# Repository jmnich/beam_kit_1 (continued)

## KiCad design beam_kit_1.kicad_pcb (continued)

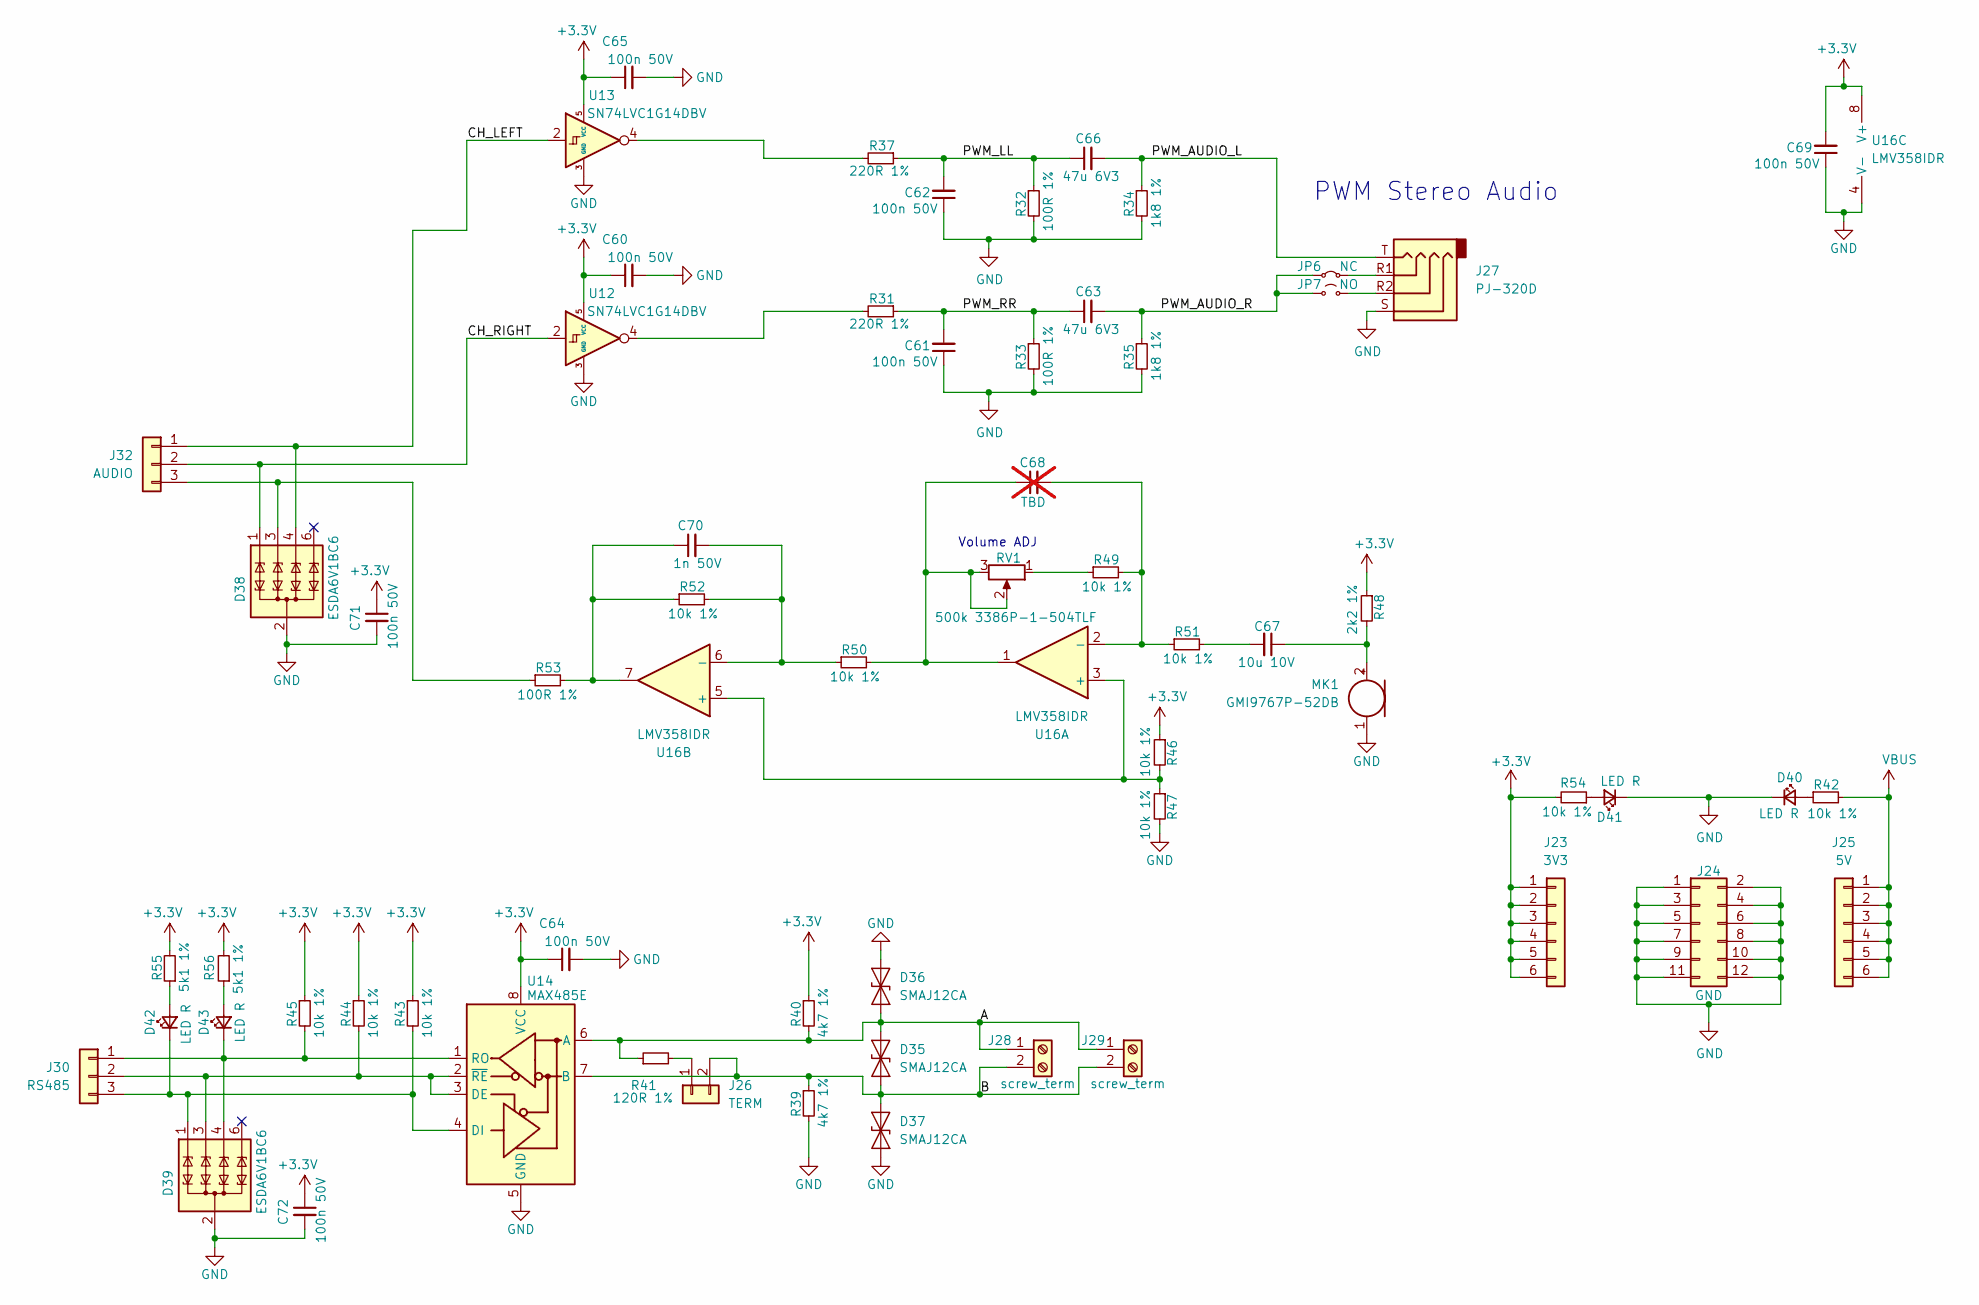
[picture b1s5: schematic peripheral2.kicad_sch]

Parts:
C60, C61, C62, C64, C65, C69, C71, C72: 100n 50V; C_0603_1608Metric_Pad1.08x0.95mm_HandSolder; jlc C14663
C63, C66: 47u 6V3; C_0805_2012Metric; jlc C16780
C67: 10u 10V; C_0603_1608Metric_Pad1.08x0.95mm_HandSolder; jlc C19702
C68: TBD; C_0603_1608Metric_Pad1.08x0.95mm_HandSolder; not fitted
C70: 1n 50V; C_0603_1608Metric_Pad1.08x0.95mm_HandSolder; jlc C1588
D35, D36, D37: SMAJ12CA; D_SMA; jlc C908818
D38, D39: ESDA6V1BC6; SOT-23-6; MPN ESDA6V1BC6; jlc C495220
D40, D41, D42, D43: LED R; LED_0603_1608Metric_Pad1.05x0.95mm_HandSolder; jlc C2286
J23: 3V3; PinHeader_1x06_P2.54mm_Vertical; jlc C37208
J24: GND; PinHeader_2x06_P2.54mm_Vertical; jlc C492423
J25: 5V; PinHeader_1x06_P2.54mm_Vertical; jlc C37208
J26: TERM; PinHeader_1x02_P2.54mm_Vertical; jlc C492401
J27: PJ-320D; Jack_3.5mm_PJ320D_Horizontal; jlc C431535
J28, J29: screw_term; TerminalBlock_Phoenix_MKDS-1,5-2-5.08_1x02_P5.08mm_Horizont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; jlc C395734
J30: RS485; PinHeader_1x03_P2.54mm_Vertical; jlc C49257
J32: AUDIO; PinHeader_1x03_P2.54mm_Vertical; jlc C49257
JP6: NC; SolderJumper-2_P1.3mm_Bridged_RoundedPad1.0x1.5mm
JP7: NO; SolderJumper-2_P1.3mm_Open_RoundedPad1.0x1.5mm
MK1: GMI9767P-52DB; PinHeader_1x02_P2.54mm_Vertical; jlc C234023
R31, R37: 220R 1%; R_0603_1608Metric_Pad0.98x0.95mm_HandSolder; jlc C22962
R32, R33, R53: 100R 1%; R_0603_1608Metric_Pad0.98x0.95mm_HandSolder; jlc C22775
R34, R35: 1k8 1%; R_0603_1608Metric_Pad0.98x0.95mm_HandSolder; jlc C4177
R39, R40: 4k7 1%; R_0603_1608Metric_Pad0.98x0.95mm_HandSolder; jlc C23162
R41: 120R 1%; R_0603_1608Metric_Pad0.98x0.95mm_HandSolder; jlc C22787
R42, R43, R44, R45, R46, R47, R49, R50, R51, R52, R54: 10k 1%; R_0603_1608Metric_Pad0.98x0.95mm_HandSolder; jlc C25804
R48: 2k2 1%; R_0603_1608Metric_Pad0.98x0.95mm_HandSolder; jlc C4190
R55, R56: 5k1 1%; R_0603_1608Metric_Pad0.98x0.95mm_HandSolder; jlc C23186
RV1: 500k 3386P-1-504TLF; Potentiometer_Bourns_3386P_Vertical; jlc C116316
U12, U13: SN74LVC1G14DBV; SOT-23-5; MPN SN74LVC1G14DBV; jlc C7835
U14: MAX485E; SOIC-8_3.9x4.9mm_P1.27mm; jlc C19738
U16: LMV358IDR; SOIC-8_3.9x4.9mm_P1.27mm; jlc C63813

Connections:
+3.3V: C60.1, C64.1, C65.1, C69.2, C71.1, C72.1, J23.1, J23.2, J23.3, J23.4, J23.5, J23.6, R40.1, R43.1, R44.1, R45.1, R46.1, R48.1, R54.2, R55.2, R56.2, U12.5 (VCC), U13.5 (VCC), U14.8 (VCC), U16.8 (V+); also elsewhere on the board
/peripheral2/A: D35.2 (A2), D36.1 (A1), J28.1, J29.1, R40.2, R41.1, U14.6 (A)
/peripheral2/B: D35.1 (A1), D37.2 (A2), J26.2, J28.2, J29.2, R39.1, U14.7 (B)
/peripheral2/CH_LEFT: D38.4 (TVS3), J32.1, U13.2
/peripheral2/CH_RIGHT: D38.1 (TVS1), J32.2, U12.2
/peripheral2/PWM_AUDIO_L: C66.2, J27.T, R34.1
/peripheral2/PWM_AUDIO_R: C63.2, JP6.1 (A), JP7.1 (A), R35.1
/peripheral2/PWM_LL: C62.2, C66.1, R32.1, R37.1
/peripheral2/PWM_RR: C61.2, C63.1, R31.1, R33.1
GND: C60.2, C61.1, C62.1, C64.2, C65.2, C69.1, C71.2, C72.2, D36.2 (A2), D37.1 (A1), D38.2 (COM), D38.5 (COM), D39.2 (COM), D39.5 (COM), D40.1 (K), D41.1 (K), J24.1, J24.2, J24.3, J24.4, J24.5, J24.6, J24.7, J24.8, J24.9, J24.10, J24.11, J24.12, J27.S, MK1.1 (-), R32.2, R33.2, R34.2, R35.2, R39.2, R47.2, U12.3 (GND), U13.3 (GND), U14.5 (GND), U16.4 (V-); also elsewhere on the board
unnamed: C67.2, R51.2
unnamed: C68.1, R50.2, RV1.2, RV1.3, U16.1
unnamed: C70.1, R52.1, R53.2, U16.7
unnamed: D38.3 (TVS2), J32.3, R53.1
unnamed: D39.1 (TVS1), D42.1 (K), J30.3, R43.2, U14.4 (DI)
unnamed: D39.3 (TVS2), J30.2, R44.2, U14.2 (~RE), U14.3 (DE)
unnamed: D39.4 (TVS3), D43.1 (K), J30.1, R45.2, U14.1 (RO)
unnamed: D40.2 (A), R42.1
unnamed: D41.2 (A), R54.1
unnamed: D42.2 (A), R55.1
unnamed: D43.2 (A), R56.1
unnamed: J26.1, R41.2
unnamed: J27.R1, JP6.2 (B)
unnamed: J27.R2, JP7.2 (B)
unnamed: C67.1, MK1.2 (+), R48.2
unnamed: R31.2, U12.4
unnamed: R37.2, U13.4
unnamed: R49.1, RV1.1
unnamed: R46.2, R47.1, U16.3 (+), U16.5 (+)
unnamed: C68.2, R49.2, R51.1, U16.2 (-)
unnamed: C70.2, R50.1, R52.2, U16.6 (-)
VBUS: J25.1, J25.2, J25.3, J25.4, J25.5, J25.6, R42.2; also elsewhere on the board

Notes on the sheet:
PWM Stereo Audio
Volume ADJ

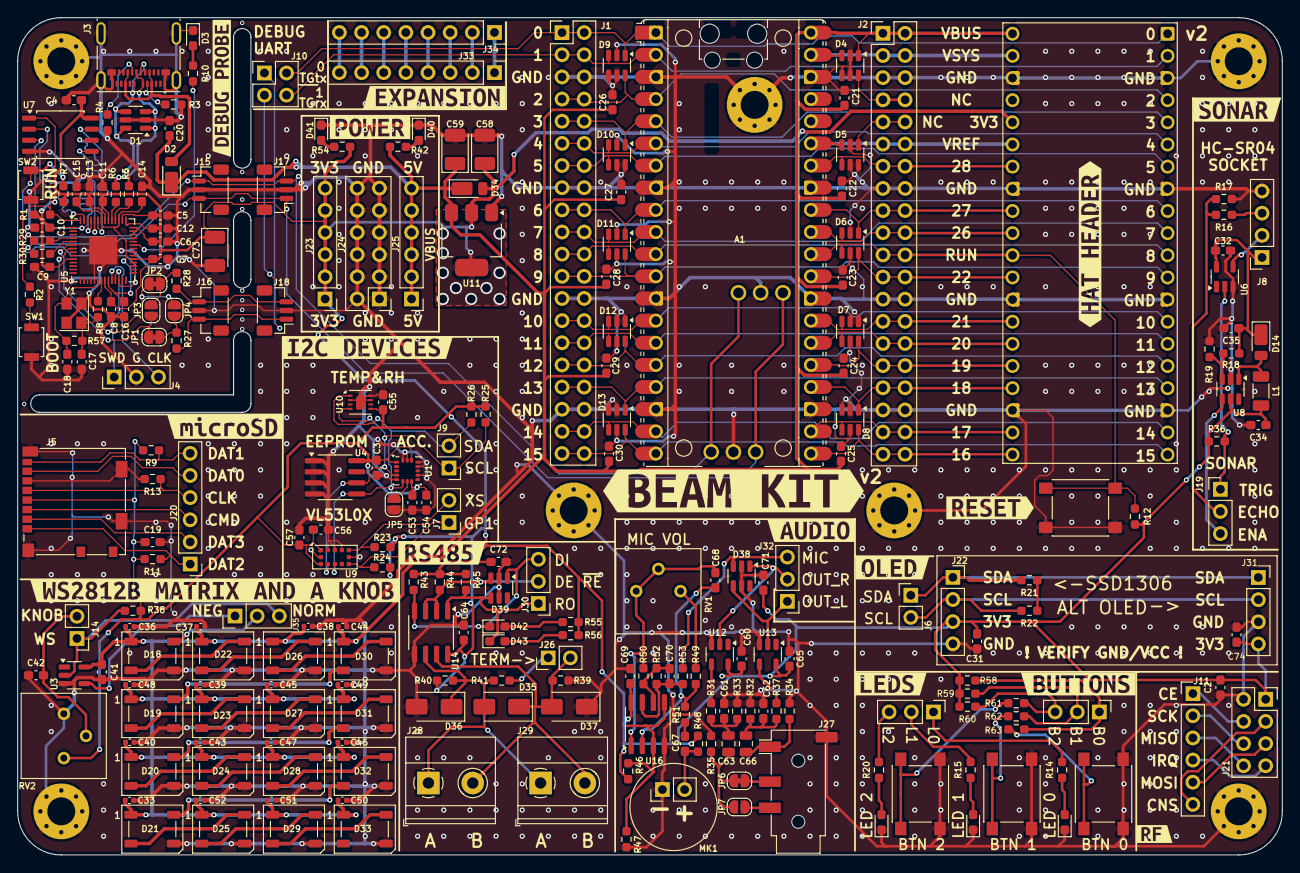
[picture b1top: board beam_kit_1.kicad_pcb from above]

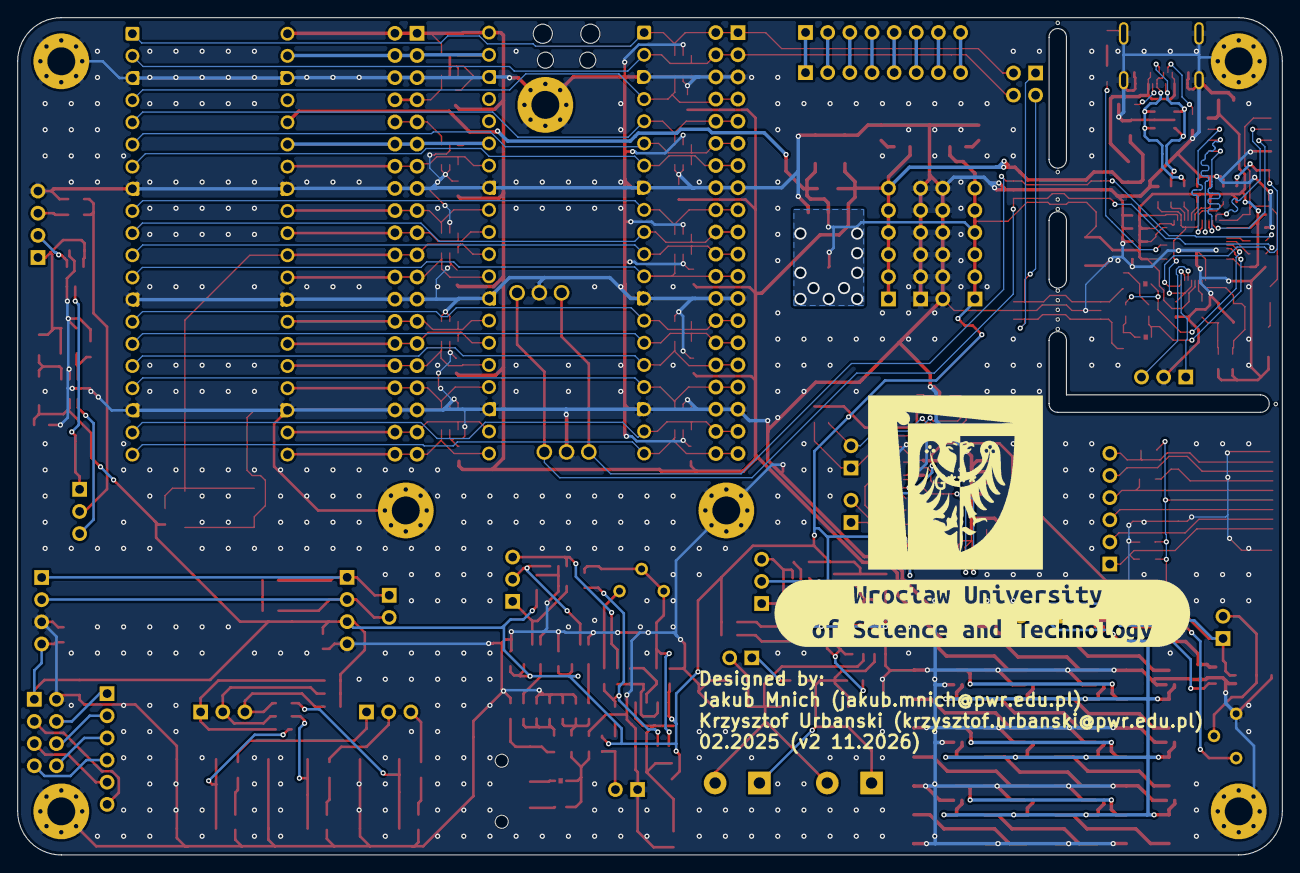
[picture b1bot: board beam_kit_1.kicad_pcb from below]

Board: 2 copper layers, 145.0 x 96.0 mm, 282 parts (2 on the bottom side), 160 nets.

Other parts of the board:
H6#2, H6#3, H6#4, H6#5, H6#6, H6#7, H6#8, H6#9, H6#10: MB template; MountingHole_2.1mm
kibuzzard-6AEDD45B: G***; kibuzzard-6AEDD45B
kibuzzard-62ECE595: G***; kibuzzard-62ECE595
kibuzzard-67BB2A6B: G***; kibuzzard-67BB2A6B
kibuzzard-67BB2A29: G***; kibuzzard-67BB2A29
kibuzzard-67BB2BB0: G***; kibuzzard-67BB2BB0
kibuzzard-67BB2C58: G***; kibuzzard-67BB2C58
kibuzzard-67BB2CB4: G***; kibuzzard-67BB2CB4
kibuzzard-67BB2CE4: G***; kibuzzard-67BB2CE4
kibuzzard-67BB2D55: G***; kibuzzard-67BB2D55
kibuzzard-67BB2DE0: G***; kibuzzard-67BB2DE0
kibuzzard-67BB2F8C: G***; kibuzzard-67BB2F8C
kibuzzard-67BB2FFD: G***; kibuzzard-67BB2FFD
kibuzzard-67BB3BA0: G***; kibuzzard-67BB3BA0
kibuzzard-67BB3D27: G***; kibuzzard-67BB3D27
kibuzzard-67BB581A: G***; kibuzzard-67BB581A
kibuzzard-67BB3747: G***; kibuzzard-67BB3747
kibuzzard-67BB4182: G***; kibuzzard-67BB4182

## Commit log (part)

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2025-02-22 fit test
2025-02-22 layout
2025-02-23 preparing for more modules
2025-02-23 more stuff added to sch
2025-02-23 kju fix and PCB size increase
2025-02-23 layout done
2025-02-23 codes and fixes
2025-02-23 RS leds fix
2025-02-23 jlc codes filled
2025-02-23 routing in progress
2025-02-24 corrections
2025-02-24 final version
2026-01-30 readme
2026-01-30 readme fix
